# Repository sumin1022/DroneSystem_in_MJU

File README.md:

# 드론을 이용한 산불 피해 산림 재생 시스템
#### 23.09 - 12  | 2023 명지대학교 융합 Festival '융합프로젝트' 부문 금상

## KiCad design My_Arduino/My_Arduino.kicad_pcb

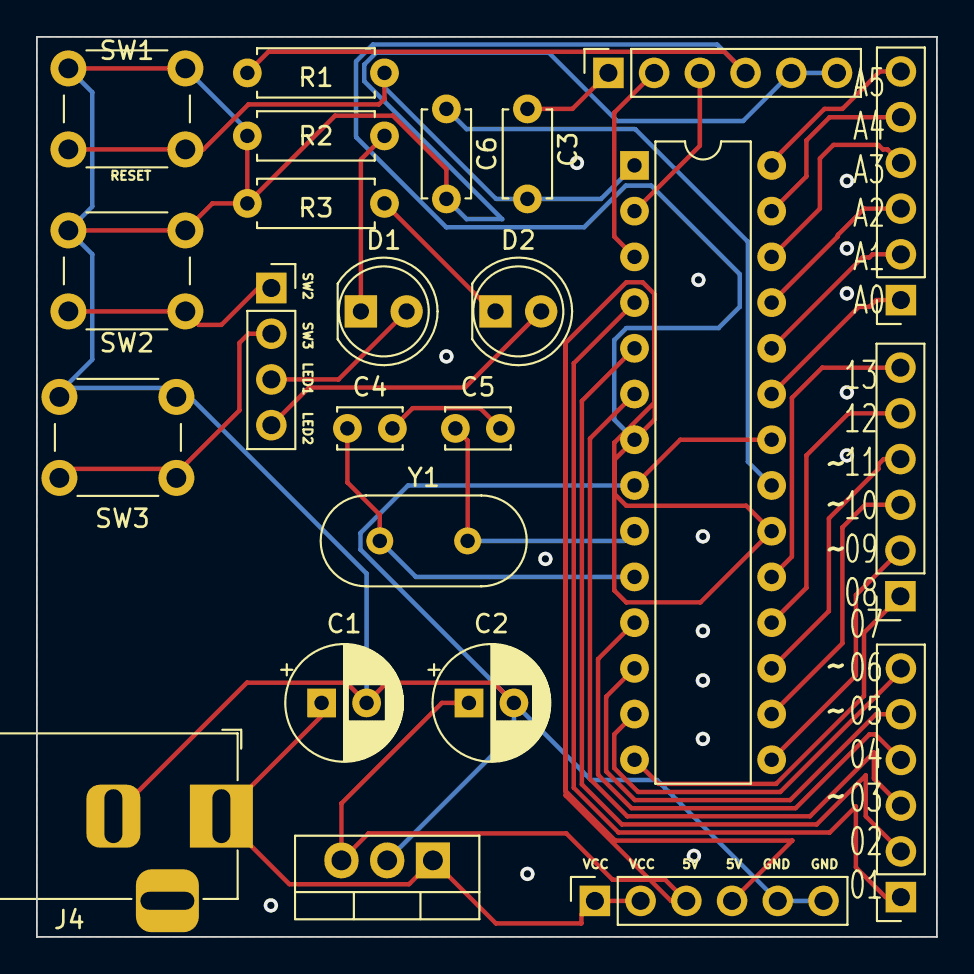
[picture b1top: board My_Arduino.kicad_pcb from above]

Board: 2 copper layers, 50.0 x 50.0 mm, 24 parts (0 on the bottom side), 35 nets.

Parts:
C1, C2: 16V_220uF; CP_Radial_D6.3mm_P2.50mm
C3, C6: 0.1uF; C_Disc_D4.7mm_W2.5mm_P5.00mm
C4, C5: 18pF; C_Disc_D3.4mm_W2.1mm_P2.50mm
D1, D2: LED; LED_D5.0mm
J1: Digital_8_13; PinSocket_1x06_P2.54mm_Vertical
J2: Analog_0_5; PinSocket_1x06_P2.54mm_Vertical
J3: Digital_2_7; PinSocket_1x06_P2.54mm_Vertical
J4: Barrel_Jack_Switch; BarrelJack_Horizontal
J5: Download; PinSocket_1x06_P2.54mm_Vertical
J6: Power; PinSocket_1x06_P2.54mm_Vertical
Je1: LED_Switch; PinSocket_1x04_P2.54mm_Vertical
R1: 10kR; R_Axial_DIN0207_L6.3mm_D2.5mm_P7.62mm_Horizontal
R2, R3: 330R; R_Axial_DIN0207_L6.3mm_D2.5mm_P7.62mm_Horizontal
SW1, SW2, SW3: SW_Push; SW_PUSH_6mm
U1: ATmega328P-P; DIP-28_W7.62mm
U2: LM7805_TO220; TO-220-3_Vertical
Y1: 16MHz; Crystal_HC49-4H_Vertical

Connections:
+5V: C2.1, J5.4, J6.3, J6.4, R1.1, U1.7 (VCC), U1.20 (AVCC), U2.3 (VO)
/DTR: C3.2, J5.1
/RESET: C3.1, R1.2, SW1.2, U1.1 (~RESET/PC6)
/RXD: J5.3, U1.2 (PD0)
/TXD: J5.2, U1.3 (PD1)
/XTAL1: C5.1, U1.9 (XTAL1/PB6), Y1.2
/XTAL2: C4.1, U1.10 (XTAL2/PB7), Y1.1
GND: C1.2, C2.2, C6.2, J4.2, J5.5, J5.6, J6.5, J6.6, R2.1, R3.1, SW1.1, SW2.1, SW3.1, U1.8 (GND), U1.22 (GND), U2.2 (GND)
unnamed: C4.2, C5.2
unnamed: D1.2 (A), Je1.3
unnamed: D1.1 (K), R2.2
unnamed: D2.2 (A), Je1.4
unnamed: D2.1 (K), R3.2
unnamed: J1.1, U1.14 (PB0)
unnamed: J1.2, U1.15 (PB1)
unnamed: J1.3, U1.16 (PB2)
unnamed: J1.4, U1.17 (PB3)
unnamed: J1.5, U1.18 (PB4)
unnamed: J1.6, U1.19 (PB5)
unnamed: J2.1, U1.23 (PC0)
unnamed: J2.2, U1.24 (PC1)
unnamed: J2.3, U1.25 (PC2)
unnamed: J2.4, U1.26 (PC3)
unnamed: J2.5, U1.27 (PC4)
unnamed: J2.6, U1.28 (PC5)
unnamed: J3.1, U1.4 (PD2)
unnamed: J3.2, U1.5 (PD3)
unnamed: J3.3, U1.6 (PD4)
unnamed: J3.4, U1.11 (PD5)
unnamed: J3.5, U1.12 (PD6)
unnamed: J3.6, U1.13 (PD7)
unnamed: Je1.1, SW2.2
unnamed: Je1.2, SW3.2
unnamed: C6.1, U1.21 (AREF)
VCC: C1.1, J4.1, J6.1, J6.2, U2.1 (VI)
